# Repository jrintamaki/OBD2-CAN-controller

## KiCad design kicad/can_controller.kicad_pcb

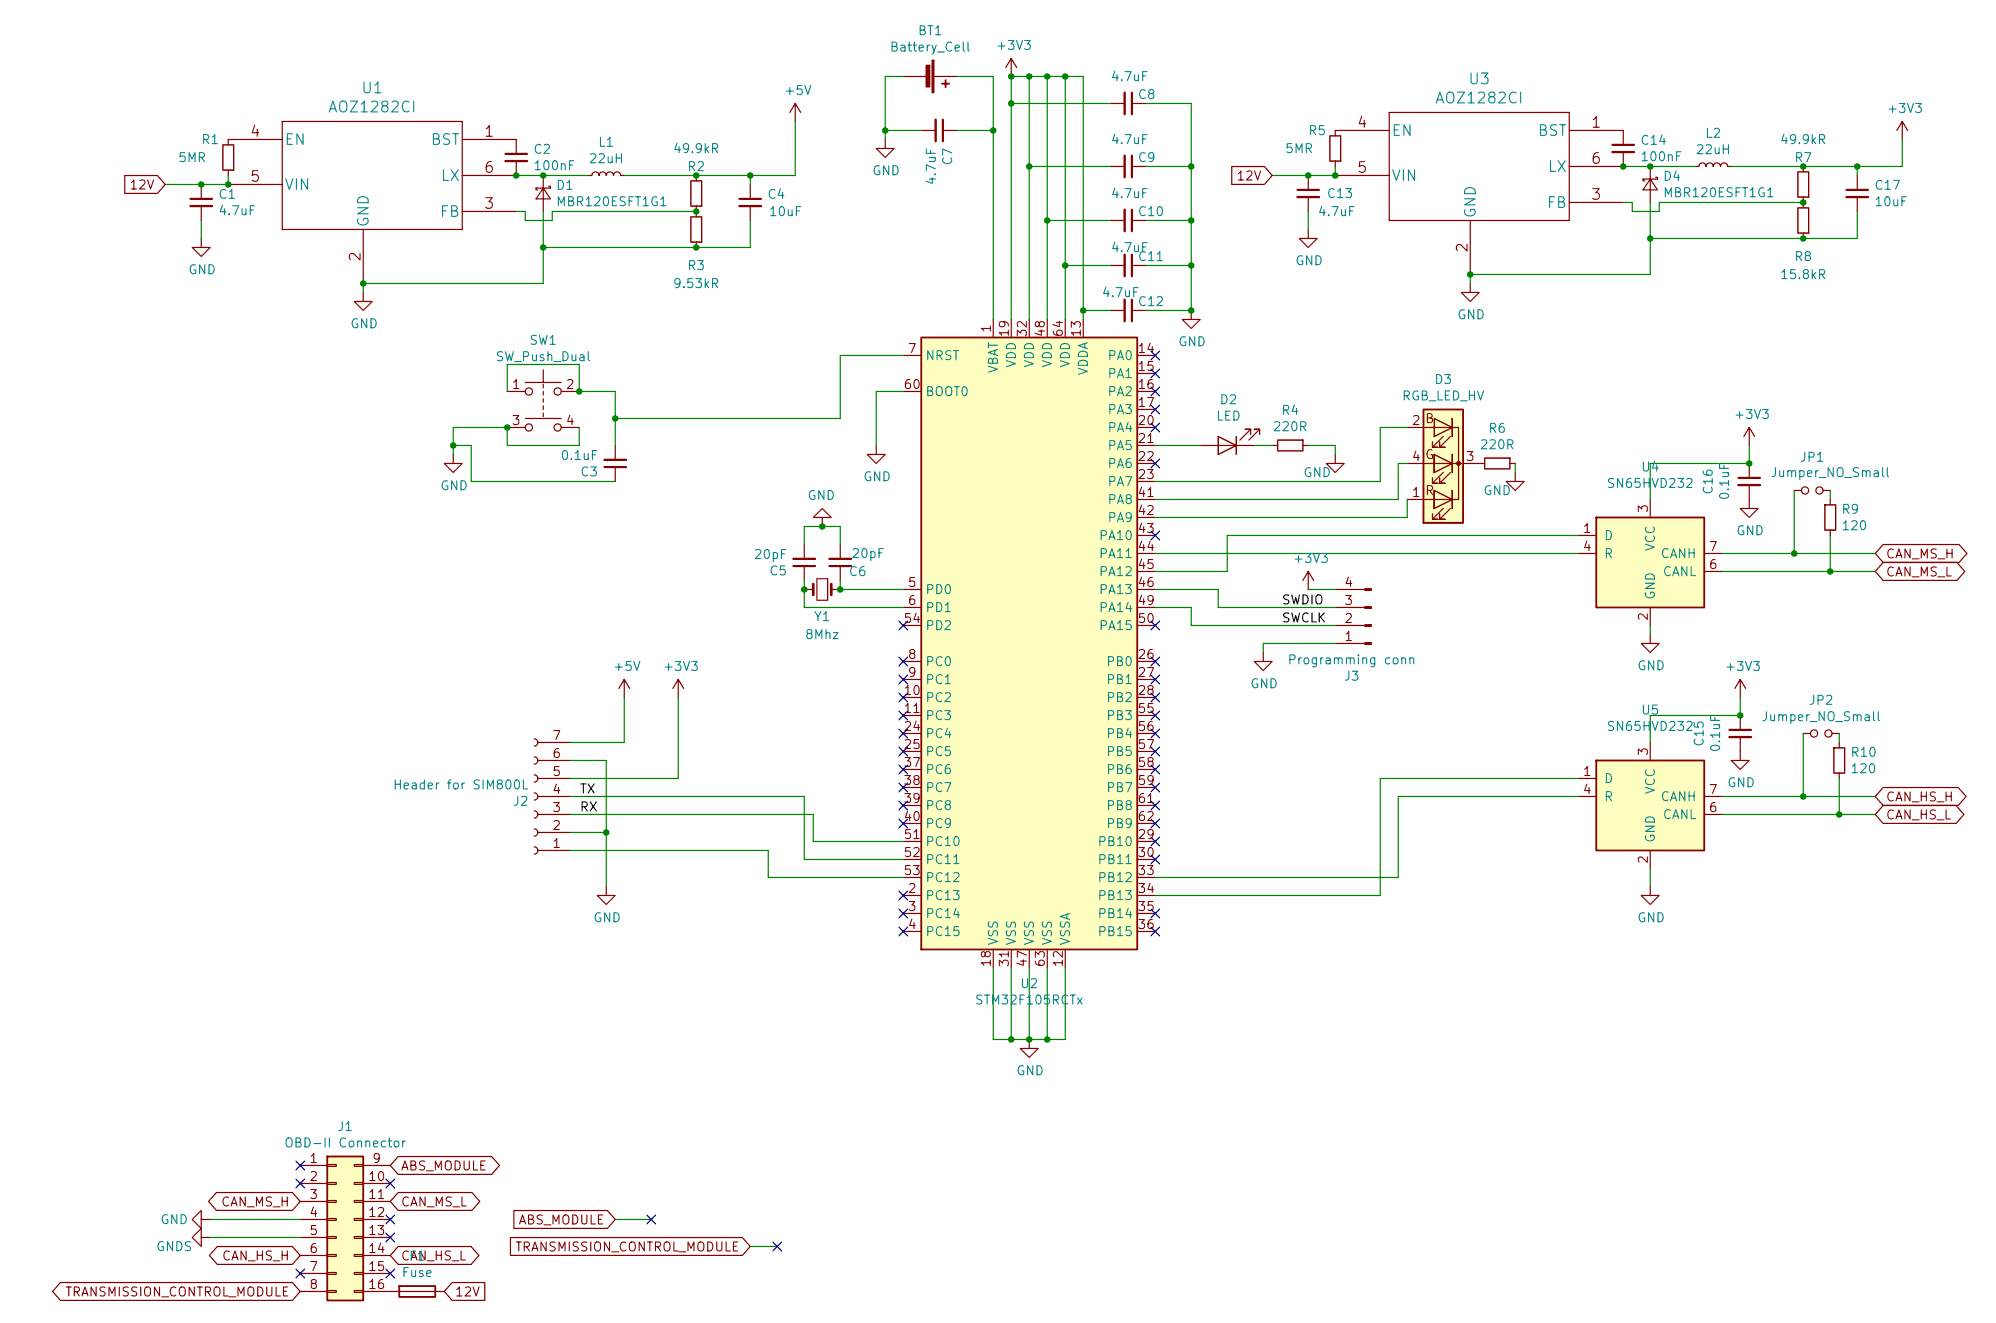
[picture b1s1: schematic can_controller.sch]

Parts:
BT1: Battery_Cell; BU2032SM-JJ-GTR
C1, C7, C8, C9, C10, C11, C12, C13: 4.7uF; C_1206_3216Metric_Pad1.42x1.75mm_HandSolder
C2, C14: 100nF; C_1206_3216Metric_Pad1.42x1.75mm_HandSolder
C3, C15, C16: 0.1uF; C_1206_3216Metric_Pad1.42x1.75mm_HandSolder
C4, C17: 10uF; C_1206_3216Metric_Pad1.42x1.75mm_HandSolder
C5, C6: 20pF; C_1206_3216Metric_Pad1.42x1.75mm_HandSolder
D1, D4: MBR120ESFT1G1; D_SOD-123F
D2: LED; LED_1206_3216Metric_Pad1.42x1.75mm_HandSolder
D3: RGB_LED_HV; HV-5RGB60
F1: Fuse; Fuse_0603_1608Metric_Pad1.05x0.95mm_HandSolder
J1: OBD-II Connector; OBDII
J2: Header for SIM800L; PinHeader_1x07_P2.00mm_Vertical
J3: Programming conn; PinHeader_1x04_P2.00mm_Vertical
JP1, JP2: Jumper_NO_Small; PinHeader_1x02_P2.00mm_Vertical
L1, L2: 22uH; R_1206_3216Metric_Pad1.42x1.75mm_HandSolder
R1, R5: 5MR; R_1206_3216Metric_Pad1.42x1.75mm_HandSolder
R2, R7: 49.9kR; R_1206_3216Metric_Pad1.42x1.75mm_HandSolder
R3: 9.53kR; R_1206_3216Metric_Pad1.42x1.75mm_HandSolder
R4, R6: 220R; R_1206_3216Metric_Pad1.42x1.75mm_HandSolder
R8: 15.8kR; R_1206_3216Metric_Pad1.42x1.75mm_HandSolder
R9, R10: 120; R_1206_3216Metric_Pad1.42x1.75mm_HandSolder
SW1: SW_Push_Dual; SW_TL3305AF260QG
U1, U3: AOZ1282CI; SO-6L_10x3.84mm_P1.27mm
U2: STM32F105RCTx; LQFP-64_10x10mm_P0.5mm
U4, U5: SN65HVD232; SOIC-8_3.9x4.9mm_P1.27mm
Y1: 8Mhz; Crystal_HC49-4H_Vertical

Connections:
12V: C1.1, C13.1, F1.1, R1.1, R5.1, U1.5 (VIN), U3.5 (VIN)
+3V3: C8.2, C9.2, C10.2, C11.2, C12.2, C15.1, C16.1, C17.1, J2.5, J3.4, L2.2, R7.2, U2.13 (VDDA), U2.19 (VDD), U2.32 (VDD), U2.48 (VDD), U2.64 (VDD), U4.3 (VCC), U5.3 (VCC)
+5V: C4.1, J2.7, L1.2, R2.2
/RX: J2.3, U2.51 (PC10)
/SWCLK: J3.2, U2.49 (PA14)
/SWDIO: J3.3, U2.46 (PA13)
/TX: J2.4, U2.52 (PC11)
ABS_MODULE: J1.9
CAN_HS_H: J1.6, JP2.1, U5.7 (CANH)
CAN_HS_L: J1.14, R10.2, U5.6 (CANL)
CAN_MS_H: J1.3, JP1.1, U4.7 (CANH)
CAN_MS_L: J1.11, R9.2, U4.6 (CANL)
GND: BT1.2 (-), C1.2, C3.1, C4.2, C5.2, C6.2, C7.2, C8.1, C9.1, C10.1, C11.1, C12.1, C13.2, C15.2, C16.2, C17.2, D1.2 (A), D4.2 (A), J1.4, J2.2, J2.6, J3.1, R3.1, R4.1, R6.1, R8.1, SW1.3, SW1.4, U1.2 (GND), U2.12 (VSSA), U2.18 (VSS), U2.31 (VSS), U2.47 (VSS), U2.60 (BOOT0), U2.63 (VSS), U3.2 (GND), U4.2 (GND), U5.2 (GND)
GNDS: J1.5
unnamed: BT1.1 (+), C7.1, U2.1 (VBAT)
unnamed: C2.1, U1.1 (BST)
unnamed: C2.2, D1.1 (K), L1.1, U1.6 (LX)
unnamed: C3.2, SW1.1, SW1.2, U2.7 (NRST)
unnamed: C5.1, U2.6 (PD1), Y1.2
unnamed: C6.1, U2.5 (PD0), Y1.1
unnamed: C14.1, U3.1 (BST)
unnamed: C14.2, D4.1 (K), L2.1, U3.6 (LX)
unnamed: D2.1 (K), R4.2
unnamed: D2.2 (A), U2.21 (PA5)
unnamed: D3.1 (RA), U2.42 (PA9)
unnamed: D3.2 (BA), U2.23 (PA7)
unnamed: D3.3 (K), R6.2
unnamed: D3.4 (GA), U2.41 (PA8)
unnamed: F1.2, J1.16
unnamed: J2.1, U2.53 (PC12)
unnamed: JP1.2, R9.1
unnamed: JP2.2, R10.1
unnamed: R1.2, U1.4 (EN)
unnamed: R2.1, R3.2, U1.3 (FB)
unnamed: R5.2, U3.4 (EN)
unnamed: R7.1, R8.2, U3.3 (FB)
unnamed: U2.33 (PB12), U5.4 (R)
unnamed: U2.34 (PB13), U5.1 (D)
unnamed: U2.44 (PA11), U4.4 (R)
unnamed: U2.45 (PA12), U4.1 (D)
TRANSMISSION_CONTROL_MODULE: J1.8

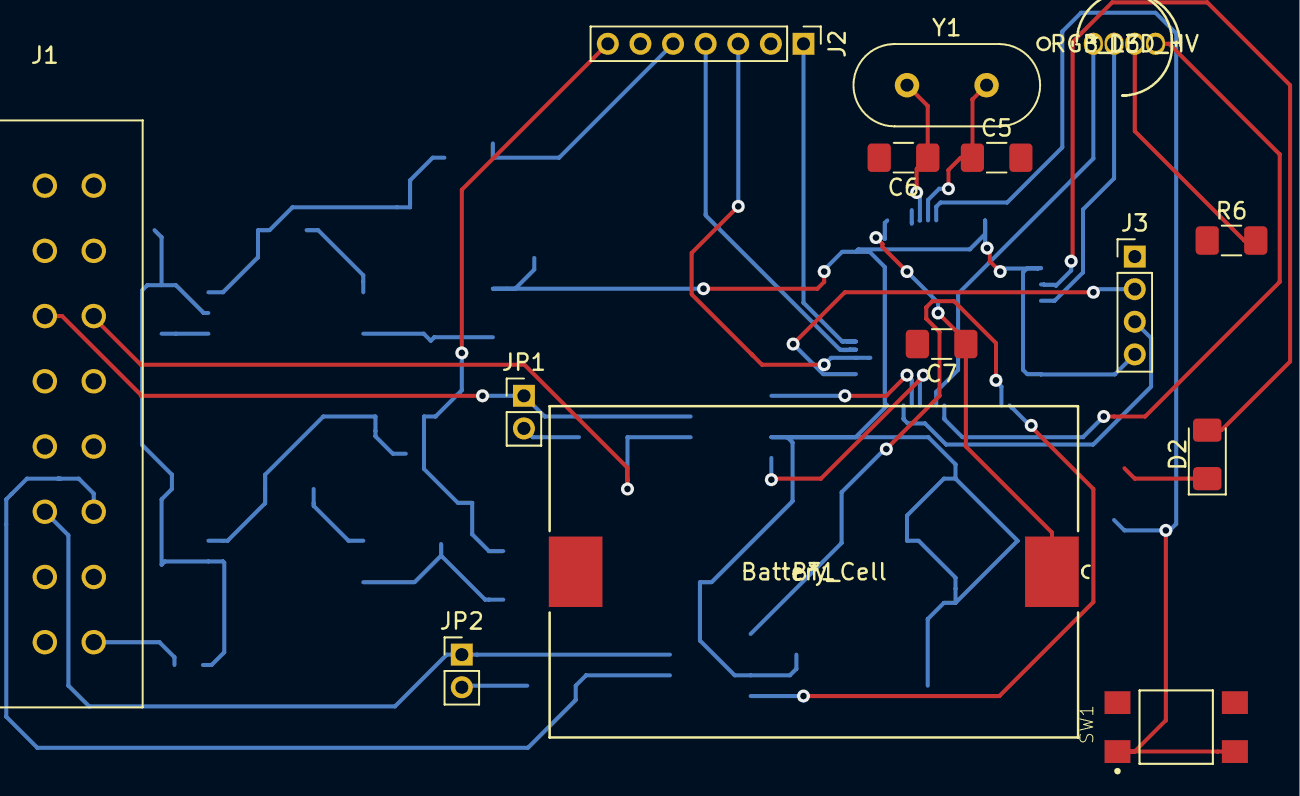
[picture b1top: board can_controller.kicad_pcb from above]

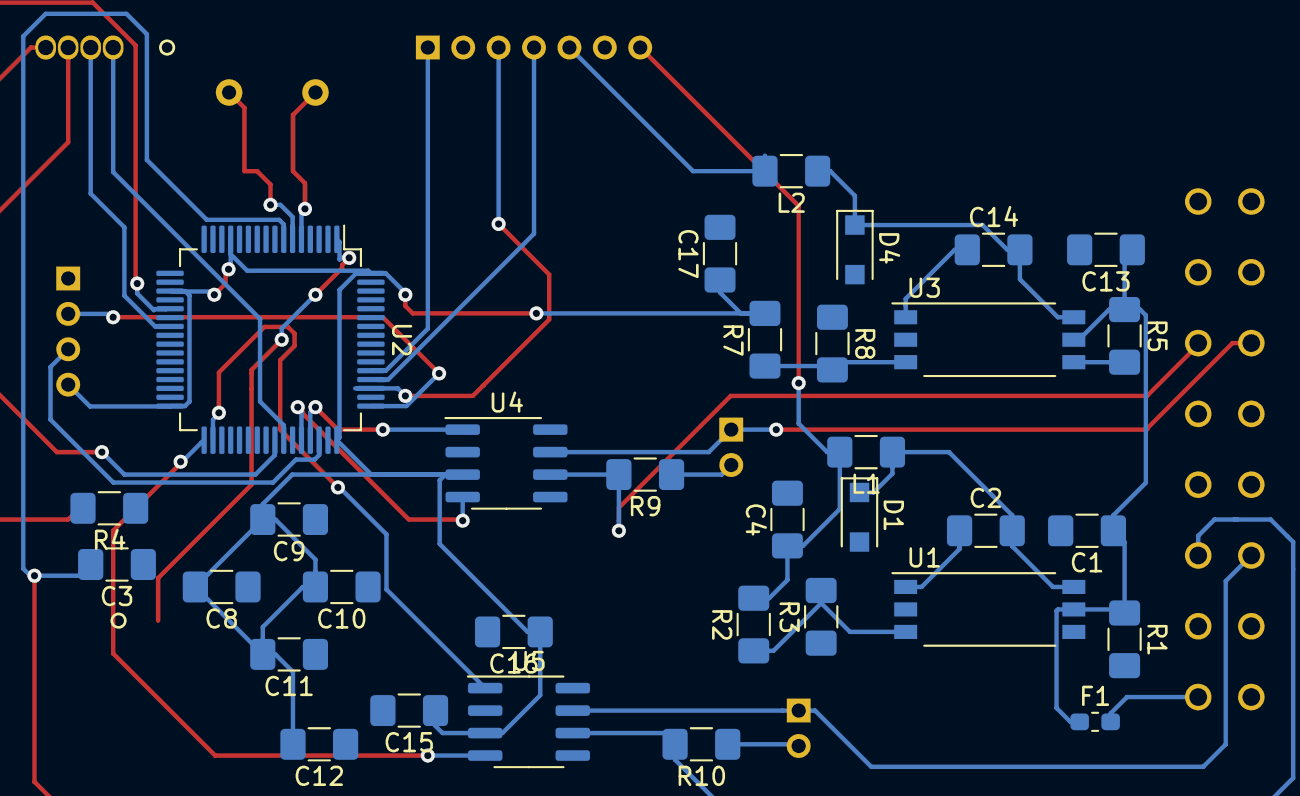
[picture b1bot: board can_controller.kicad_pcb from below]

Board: 2 copper layers, 47 parts (33 on the bottom side), 38 nets.

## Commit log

2020-02-07 Add kicad folder
2020-02-12 Add first schemas
2020-02-12 Add .gitignore file
2020-02-12 Add regulator library
2020-02-12 Add power
2020-02-12 Remove files and update .gitignore
2020-02-13 Update kicad files
2020-02-13 Add programming and sim headers
2020-02-21 Add 16 pin OBD2 socket wiring
2020-02-21 Add power led
2020-02-21 Finalize schema
2021-01-12 Jotain on tehty ehkä
2021-01-16 Finalize schema. Add and assign footprints. Start PCB layout. It's a mess...

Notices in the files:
parts and their libraries:
Copyright 2016 Accelerated Designs. All rights reserved.
